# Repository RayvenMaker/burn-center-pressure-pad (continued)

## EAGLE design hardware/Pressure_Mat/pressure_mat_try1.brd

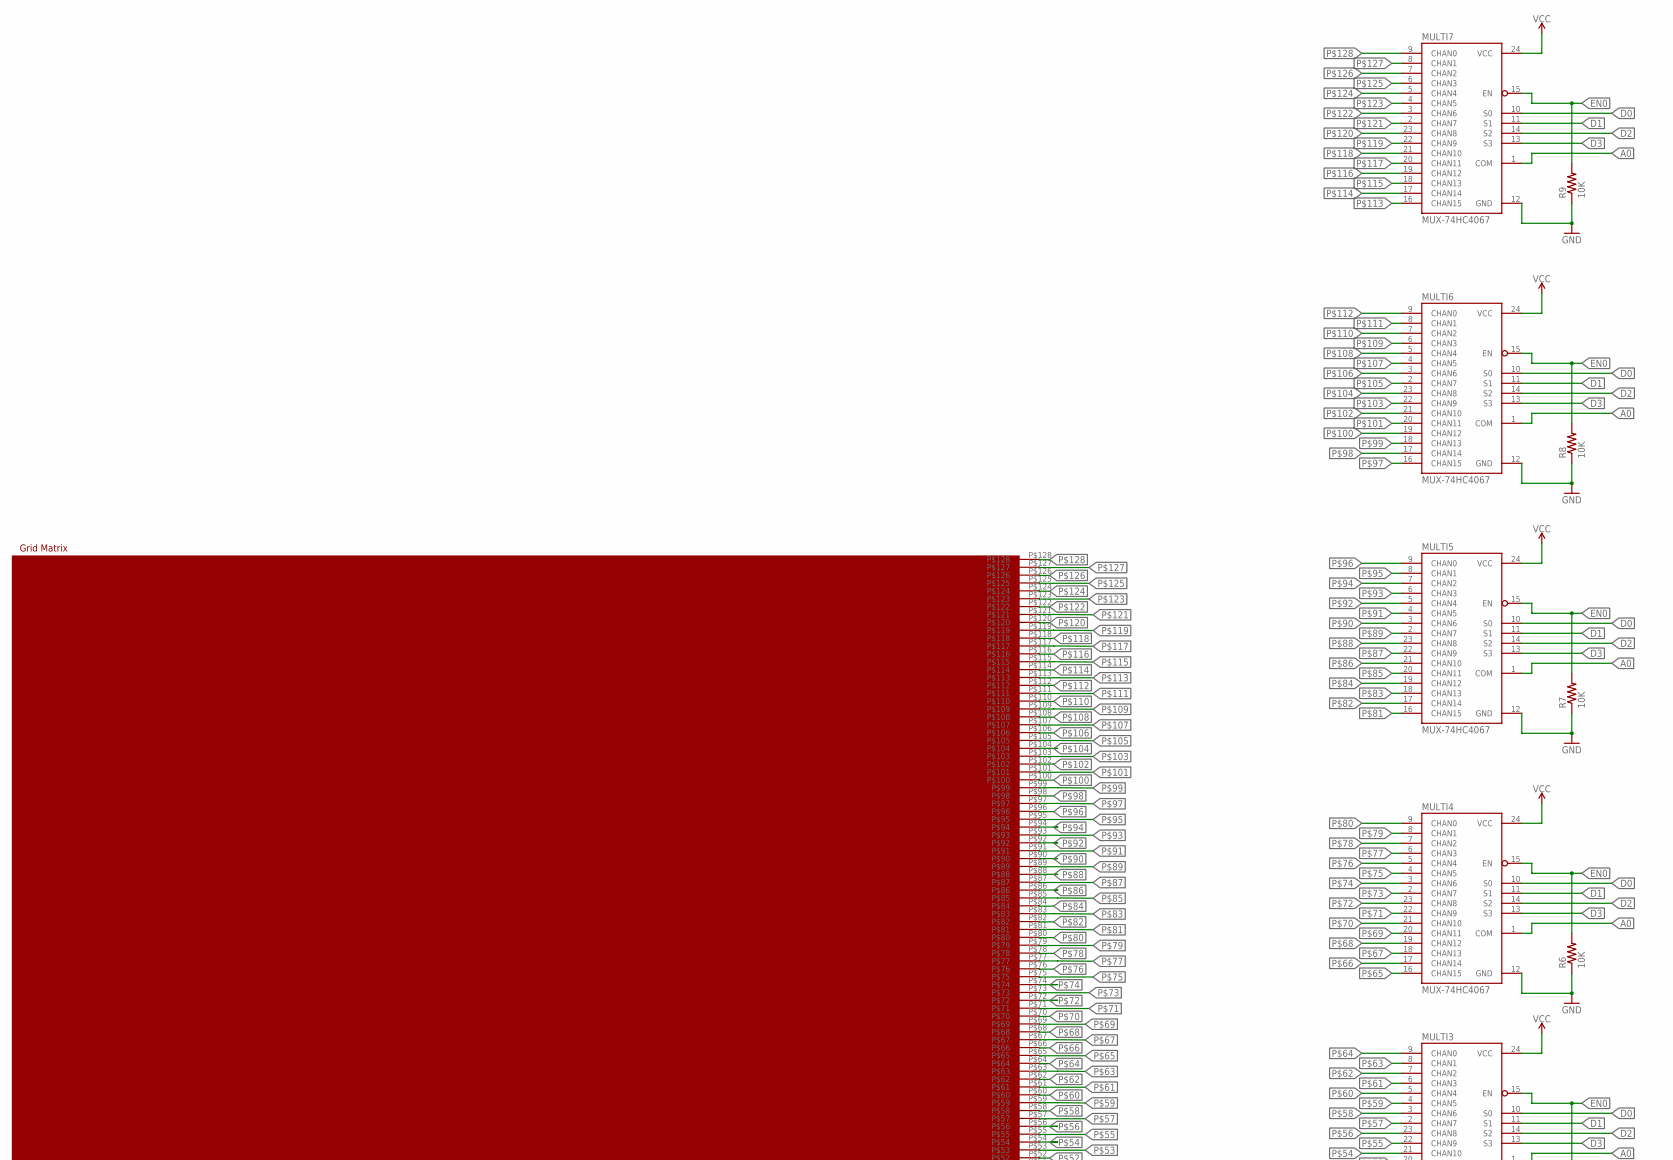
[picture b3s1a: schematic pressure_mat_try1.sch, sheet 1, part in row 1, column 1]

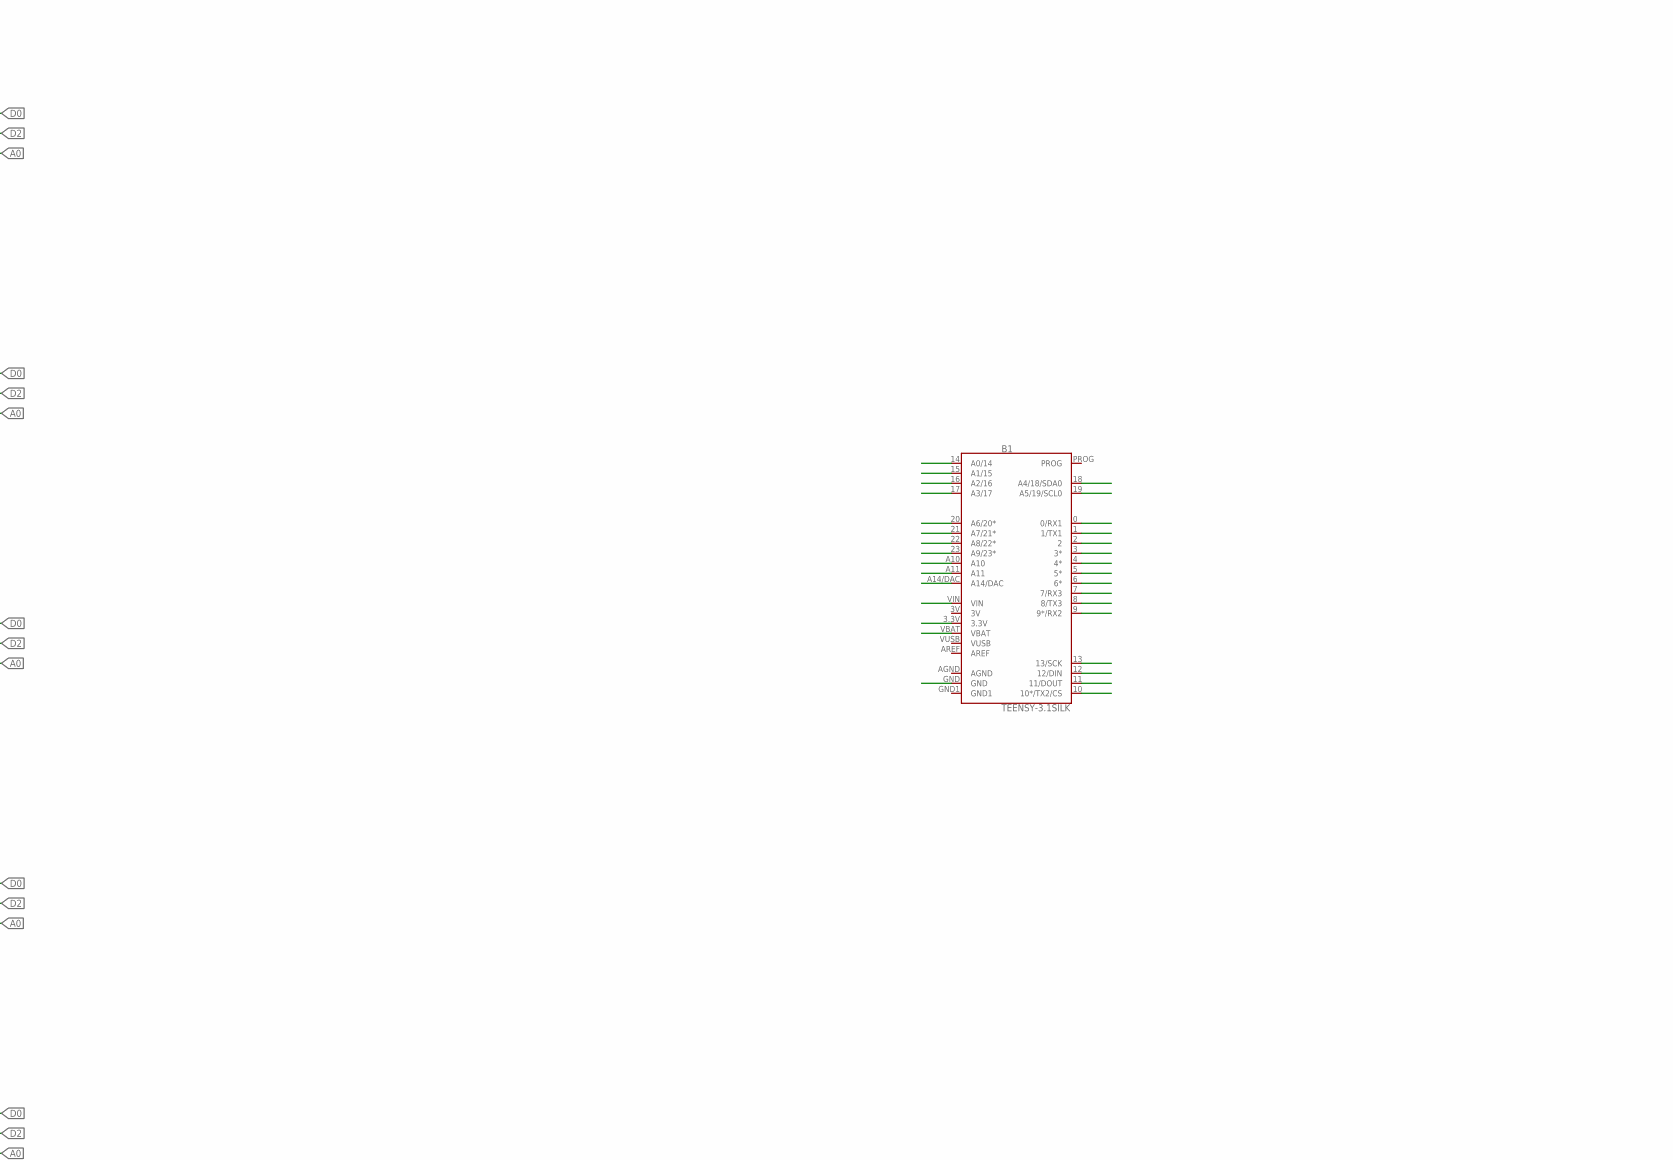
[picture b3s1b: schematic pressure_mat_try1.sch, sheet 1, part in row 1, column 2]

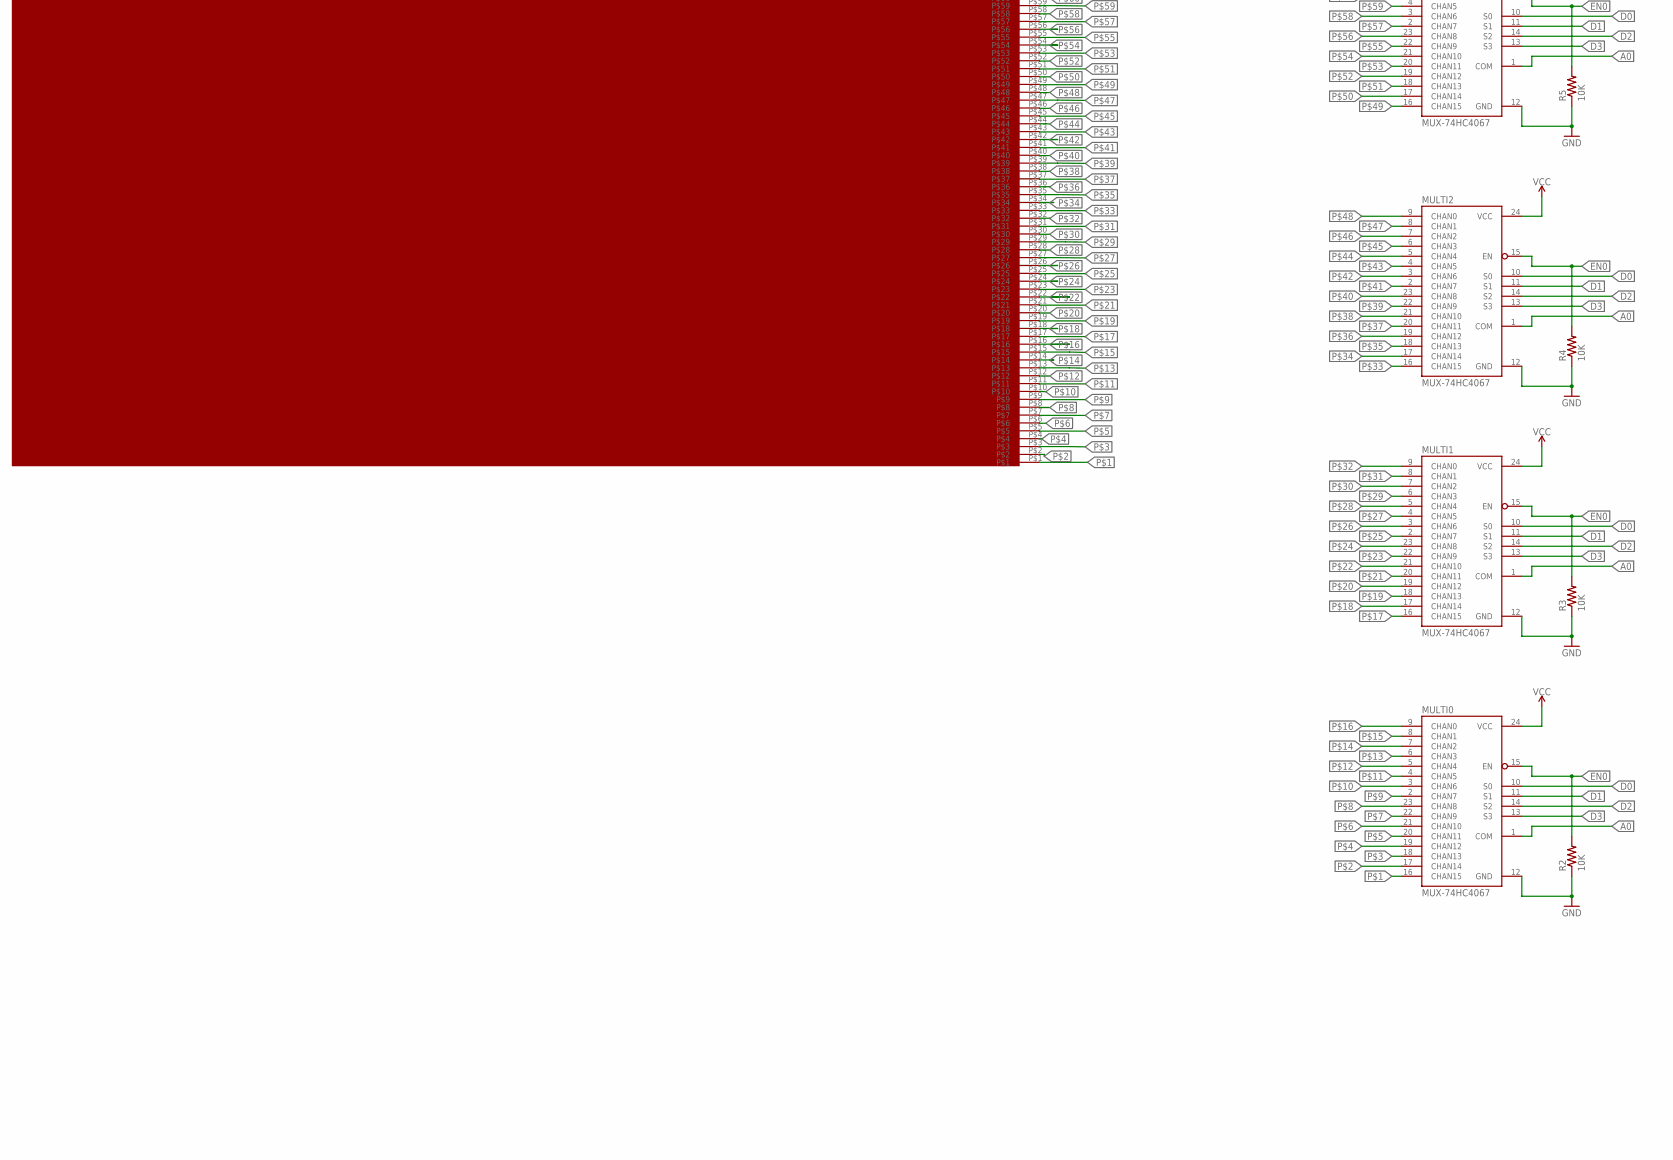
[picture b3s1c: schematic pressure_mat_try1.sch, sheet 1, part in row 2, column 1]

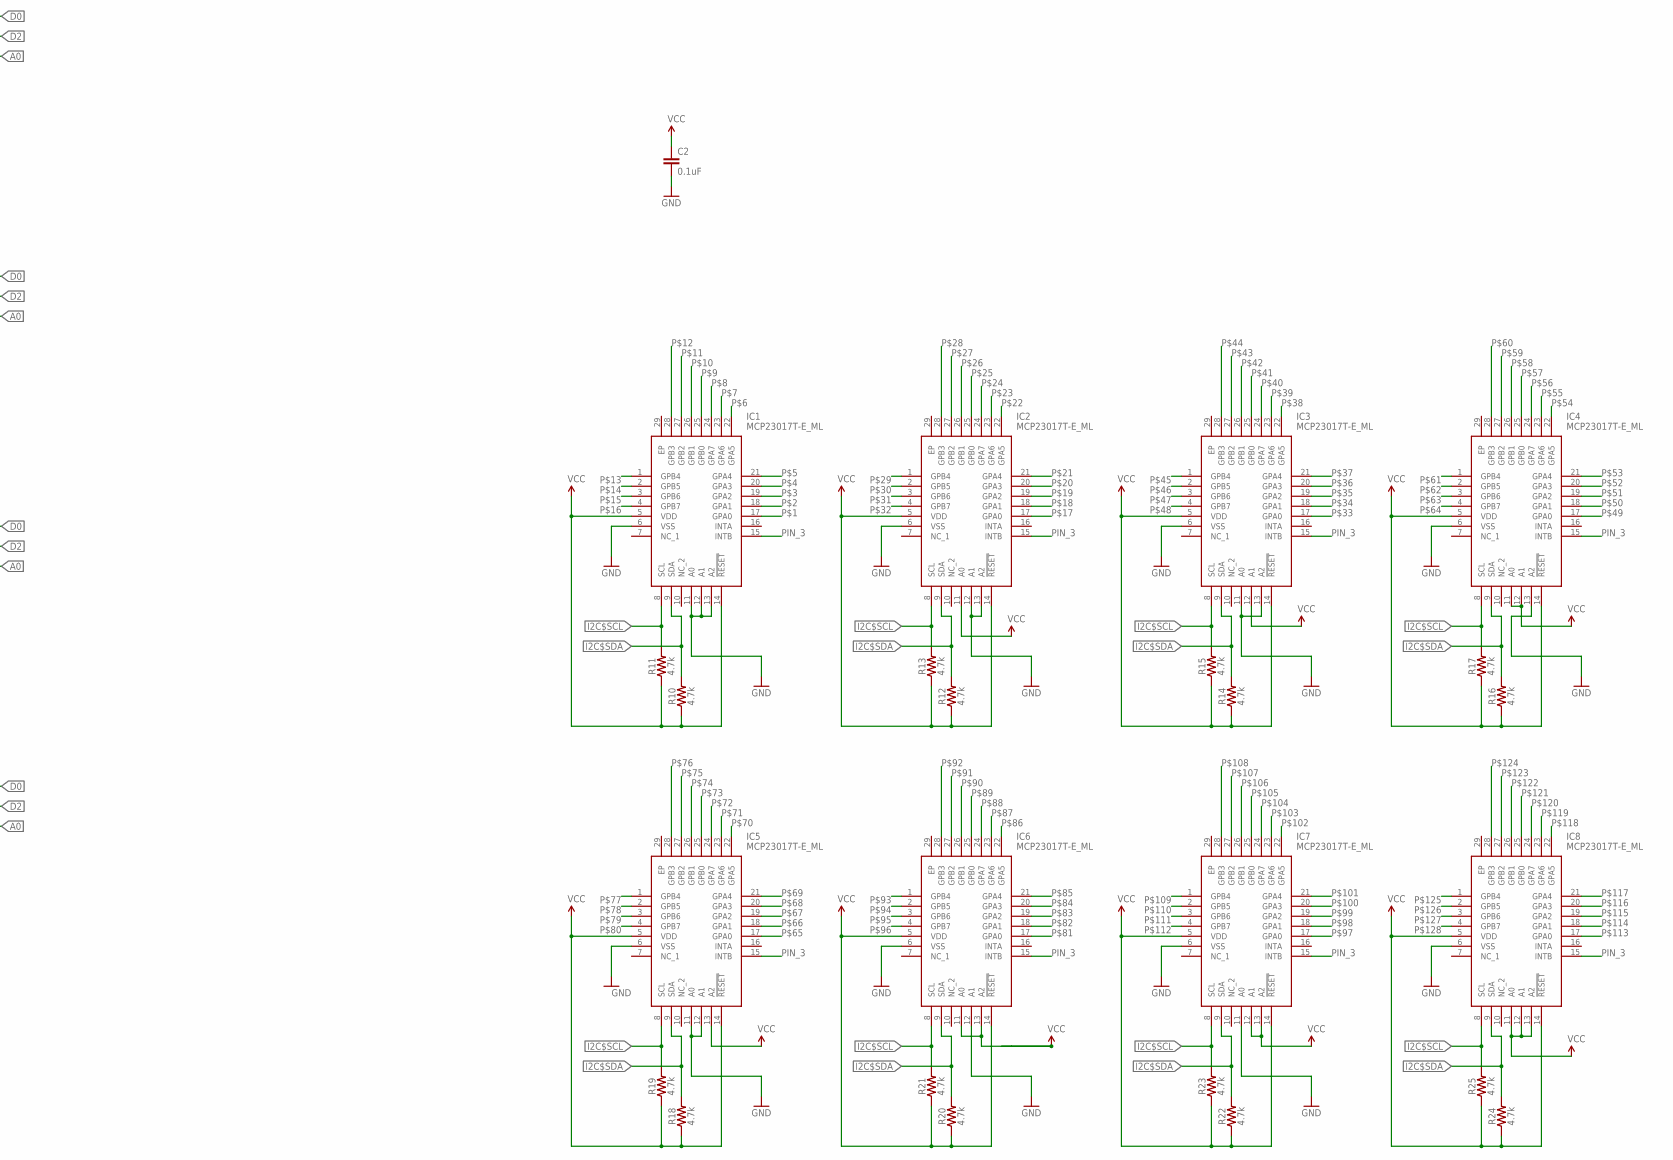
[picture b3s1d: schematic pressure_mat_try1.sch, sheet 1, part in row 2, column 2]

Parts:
B1: TEENSY-3.1SILK; TEENSY-3.1
C2: 0.1uF; 0603
IC1, IC2, IC3, IC4, IC5, IC6, IC7, IC8: MCP23017T-E_ML; QFN65P600X600X100-29N
MULTI0, MULTI1, MULTI2, MULTI3, MULTI4, MULTI5, MULTI6, MULTI7: MUX-74HC4067; SSOP24
R2, R3, R4, R5, R6, R7, R8, R9: 10K; 0603
R10, R11, R12, R13, R14, R15, R16, R17, R18, R19, R20, R21, R22, R23, R24, R25: 4.7k; 0603
U$3: SENSOR_GRID_V1.0

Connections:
3V: B1.3V
A0: MULTI0.1 (COM), MULTI1.1 (COM), MULTI2.1 (COM), MULTI3.1 (COM), MULTI4.1 (COM), MULTI5.1 (COM), MULTI6.1 (COM), MULTI7.1 (COM)
AGND: B1.AGND
D0: MULTI0.10 (S0), MULTI1.10 (S0), MULTI2.10 (S0), MULTI3.10 (S0), MULTI4.10 (S0), MULTI5.10 (S0), MULTI6.10 (S0), MULTI7.10 (S0)
D1: MULTI0.11 (S1), MULTI1.11 (S1), MULTI2.11 (S1), MULTI3.11 (S1), MULTI4.11 (S1), MULTI5.11 (S1), MULTI6.11 (S1), MULTI7.11 (S1)
D2: MULTI0.14 (S2), MULTI1.14 (S2), MULTI2.14 (S2), MULTI3.14 (S2), MULTI4.14 (S2), MULTI5.14 (S2), MULTI6.14 (S2), MULTI7.14 (S2)
D3: MULTI0.13 (S3), MULTI1.13 (S3), MULTI2.13 (S3), MULTI3.13 (S3), MULTI4.13 (S3), MULTI5.13 (S3), MULTI6.13 (S3), MULTI7.13 (S3)
EN0: MULTI0.15 (EN), MULTI1.15 (EN), MULTI2.15 (EN), MULTI3.15 (EN), MULTI4.15 (EN), MULTI5.15 (EN), MULTI6.15 (EN), MULTI7.15 (EN), R2.2, R3.2, R4.2, R5.2, R6.2, R7.2, R8.2, R9.2
GND: C2.2, IC1.6 (VSS), IC1.11 (A0), IC1.12 (A1), IC1.13 (A2), IC2.6 (VSS), IC2.12 (A1), IC2.13 (A2), IC3.6 (VSS), IC3.11 (A0), IC3.13 (A2), IC4.6 (VSS), IC4.13 (A2), IC5.6 (VSS), IC5.11 (A0), IC5.12 (A1), IC6.6 (VSS), IC6.12 (A1), IC7.6 (VSS), IC7.11 (A0), IC8.6 (VSS), MULTI0.12 (GND), MULTI1.12 (GND), MULTI2.12 (GND), MULTI3.12 (GND), MULTI4.12 (GND), MULTI5.12 (GND), MULTI6.12 (GND), MULTI7.12 (GND), R2.1, R3.1, R4.1, R5.1, R6.1, R7.1, R8.1, R9.1; also elsewhere on the board
GND1: B1.GND1
I2C$SCL: IC1.8 (SCL), IC2.8 (SCL), IC3.8 (SCL), IC4.8 (SCL), IC5.8 (SCL), IC6.8 (SCL), IC7.8 (SCL), IC8.8 (SCL), R11.2, R13.2, R15.2, R17.2, R19.2, R21.2, R23.2, R25.2
I2C$SDA: IC1.9 (SDA), IC2.9 (SDA), IC3.9 (SDA), IC4.9 (SDA), IC5.9 (SDA), IC6.9 (SDA), IC7.9 (SDA), IC8.9 (SDA), R10.2, R12.2, R14.2, R16.2, R18.2, R20.2, R22.2, R24.2
P$1: IC1.17 (GPA0), MULTI0.16 (CHAN15), U$3.P$1
P$2: IC1.18 (GPA1), MULTI0.17 (CHAN14), U$3.P$2
P$3: IC1.19 (GPA2), MULTI0.18 (CHAN13), U$3.P$3
P$4: IC1.20 (GPA3), MULTI0.19 (CHAN12), U$3.P$4
P$5: IC1.21 (GPA4), MULTI0.20 (CHAN11), U$3.P$5
P$6: IC1.22 (GPA5), MULTI0.21 (CHAN10), U$3.P$6
P$7: IC1.23 (GPA6), MULTI0.22 (CHAN9), U$3.P$7
P$8: IC1.24 (GPA7), MULTI0.23 (CHAN8), U$3.P$8
P$9: IC1.25 (GPB0), MULTI0.2 (CHAN7), U$3.P$9
P$10: IC1.26 (GPB1), MULTI0.3 (CHAN6), U$3.P$10
P$11: IC1.27 (GPB2), MULTI0.4 (CHAN5), U$3.P$11
P$12: IC1.28 (GPB3), MULTI0.5 (CHAN4), U$3.P$12
P$13: IC1.1 (GPB4), MULTI0.6 (CHAN3), U$3.P$13
P$14: IC1.2 (GPB5), MULTI0.7 (CHAN2), U$3.P$14
P$15: IC1.3 (GPB6), MULTI0.8 (CHAN1), U$3.P$15
P$16: IC1.4 (GPB7), MULTI0.9 (CHAN0), U$3.P$16
P$17: IC2.17 (GPA0), MULTI1.16 (CHAN15), U$3.P$17
P$18: IC2.18 (GPA1), MULTI1.17 (CHAN14), U$3.P$18
P$19: IC2.19 (GPA2), MULTI1.18 (CHAN13), U$3.P$19
P$20: IC2.20 (GPA3), MULTI1.19 (CHAN12), U$3.P$20
P$21: IC2.21 (GPA4), MULTI1.20 (CHAN11), U$3.P$21
P$22: IC2.22 (GPA5), MULTI1.21 (CHAN10), U$3.P$22
P$23: IC2.23 (GPA6), MULTI1.22 (CHAN9), U$3.P$23
P$24: IC2.24 (GPA7), MULTI1.23 (CHAN8), U$3.P$24
P$25: IC2.25 (GPB0), MULTI1.2 (CHAN7), U$3.P$25
P$26: IC2.26 (GPB1), MULTI1.3 (CHAN6), U$3.P$26
P$27: IC2.27 (GPB2), MULTI1.4 (CHAN5), U$3.P$27
P$28: IC2.28 (GPB3), MULTI1.5 (CHAN4), U$3.P$28
P$29: IC2.1 (GPB4), MULTI1.6 (CHAN3), U$3.P$29
P$30: IC2.2 (GPB5), MULTI1.7 (CHAN2), U$3.P$30
P$31: IC2.3 (GPB6), MULTI1.8 (CHAN1), U$3.P$31
P$32: IC2.4 (GPB7), MULTI1.9 (CHAN0), U$3.P$32
P$33: IC3.17 (GPA0), MULTI2.16 (CHAN15), U$3.P$33
P$34: IC3.18 (GPA1), MULTI2.17 (CHAN14), U$3.P$34
P$35: IC3.19 (GPA2), MULTI2.18 (CHAN13), U$3.P$35
P$36: IC3.20 (GPA3), MULTI2.19 (CHAN12), U$3.P$36
P$37: IC3.21 (GPA4), MULTI2.20 (CHAN11), U$3.P$37
P$38: IC3.22 (GPA5), MULTI2.21 (CHAN10), U$3.P$38
P$39: IC3.23 (GPA6), MULTI2.22 (CHAN9), U$3.P$39
P$40: IC3.24 (GPA7), MULTI2.23 (CHAN8), U$3.P$40
P$41: IC3.25 (GPB0), MULTI2.2 (CHAN7), U$3.P$41
P$42: IC3.26 (GPB1), MULTI2.3 (CHAN6), U$3.P$42
P$43: IC3.27 (GPB2), MULTI2.4 (CHAN5), U$3.P$43
P$44: IC3.28 (GPB3), MULTI2.5 (CHAN4), U$3.P$44
P$45: IC3.1 (GPB4), MULTI2.6 (CHAN3), U$3.P$45
P$46: IC3.2 (GPB5), MULTI2.7 (CHAN2), U$3.P$46
P$47: IC3.3 (GPB6), MULTI2.8 (CHAN1), U$3.P$47
P$48: IC3.4 (GPB7), MULTI2.9 (CHAN0), U$3.P$48
P$49: IC4.17 (GPA0), MULTI3.16 (CHAN15), U$3.P$49
P$50: IC4.18 (GPA1), MULTI3.17 (CHAN14), U$3.P$50
P$51: IC4.19 (GPA2), MULTI3.18 (CHAN13), U$3.P$51
P$52: IC4.20 (GPA3), MULTI3.19 (CHAN12), U$3.P$52
P$53: IC4.21 (GPA4), MULTI3.20 (CHAN11), U$3.P$53
P$54: IC4.22 (GPA5), MULTI3.21 (CHAN10), U$3.P$54
P$55: IC4.23 (GPA6), MULTI3.22 (CHAN9), U$3.P$55
P$56: IC4.24 (GPA7), MULTI3.23 (CHAN8), U$3.P$56
P$57: IC4.25 (GPB0), MULTI3.2 (CHAN7), U$3.P$57
P$58: IC4.26 (GPB1), MULTI3.3 (CHAN6), U$3.P$58
P$59: IC4.27 (GPB2), MULTI3.4 (CHAN5), U$3.P$59
P$60: IC4.28 (GPB3), MULTI3.5 (CHAN4), U$3.P$60
P$61: IC4.1 (GPB4), MULTI3.6 (CHAN3), U$3.P$61
P$62: IC4.2 (GPB5), MULTI3.7 (CHAN2), U$3.P$62
P$63: IC4.3 (GPB6), MULTI3.8 (CHAN1), U$3.P$63
P$64: IC4.4 (GPB7), MULTI3.9 (CHAN0), U$3.P$64
P$65: IC5.17 (GPA0), MULTI4.16 (CHAN15), U$3.P$65
P$66: IC5.18 (GPA1), MULTI4.17 (CHAN14), U$3.P$66
P$67: IC5.19 (GPA2), MULTI4.18 (CHAN13), U$3.P$67
P$68: IC5.20 (GPA3), MULTI4.19 (CHAN12), U$3.P$68
P$69: IC5.21 (GPA4), MULTI4.20 (CHAN11), U$3.P$69
P$70: IC5.22 (GPA5), MULTI4.21 (CHAN10), U$3.P$70
P$71: IC5.23 (GPA6), MULTI4.22 (CHAN9), U$3.P$71
P$72: IC5.24 (GPA7), MULTI4.23 (CHAN8), U$3.P$72
P$73: IC5.25 (GPB0), MULTI4.2 (CHAN7), U$3.P$73
P$74: IC5.26 (GPB1), MULTI4.3 (CHAN6), U$3.P$74
P$75: IC5.27 (GPB2), MULTI4.4 (CHAN5), U$3.P$75
P$76: IC5.28 (GPB3), MULTI4.5 (CHAN4), U$3.P$76
P$77: IC5.1 (GPB4), MULTI4.6 (CHAN3), U$3.P$77
P$78: IC5.2 (GPB5), MULTI4.7 (CHAN2), U$3.P$78
P$79: IC5.3 (GPB6), MULTI4.8 (CHAN1), U$3.P$79
P$80: IC5.4 (GPB7), MULTI4.9 (CHAN0), U$3.P$80
P$81: IC6.17 (GPA0), MULTI5.16 (CHAN15), U$3.P$81
P$82: IC6.18 (GPA1), MULTI5.17 (CHAN14), U$3.P$82
P$83: IC6.19 (GPA2), MULTI5.18 (CHAN13), U$3.P$83
P$84: IC6.20 (GPA3), MULTI5.19 (CHAN12), U$3.P$84
P$85: IC6.21 (GPA4), MULTI5.20 (CHAN11), U$3.P$85
P$86: IC6.22 (GPA5), MULTI5.21 (CHAN10), U$3.P$86
P$87: IC6.23 (GPA6), MULTI5.22 (CHAN9), U$3.P$87
P$88: IC6.24 (GPA7), MULTI5.23 (CHAN8), U$3.P$88
P$89: IC6.25 (GPB0), MULTI5.2 (CHAN7), U$3.P$89
P$90: IC6.26 (GPB1), MULTI5.3 (CHAN6), U$3.P$90
P$91: IC6.27 (GPB2), MULTI5.4 (CHAN5), U$3.P$91
P$92: IC6.28 (GPB3), MULTI5.5 (CHAN4), U$3.P$92
P$93: IC6.1 (GPB4), MULTI5.6 (CHAN3), U$3.P$93
P$94: IC6.2 (GPB5), MULTI5.7 (CHAN2), U$3.P$94
P$95: IC6.3 (GPB6), MULTI5.8 (CHAN1), U$3.P$95
P$96: IC6.4 (GPB7), MULTI5.9 (CHAN0), U$3.P$96
P$97: IC7.17 (GPA0), MULTI6.16 (CHAN15), U$3.P$97
P$98: IC7.18 (GPA1), MULTI6.17 (CHAN14), U$3.P$98
P$99: IC7.19 (GPA2), MULTI6.18 (CHAN13), U$3.P$99
P$100: IC7.20 (GPA3), MULTI6.19 (CHAN12), U$3.P$100
P$101: IC7.21 (GPA4), MULTI6.20 (CHAN11), U$3.P$101
P$102: IC7.22 (GPA5), MULTI6.21 (CHAN10), U$3.P$102
P$103: IC7.23 (GPA6), MULTI6.22 (CHAN9), U$3.P$103
P$104: IC7.24 (GPA7), MULTI6.23 (CHAN8), U$3.P$104
P$105: IC7.25 (GPB0), MULTI6.2 (CHAN7), U$3.P$105
P$106: IC7.26 (GPB1), MULTI6.3 (CHAN6), U$3.P$106
P$107: IC7.27 (GPB2), MULTI6.4 (CHAN5), U$3.P$107
P$108: IC7.28 (GPB3), MULTI6.5 (CHAN4), U$3.P$108
P$109: IC7.1 (GPB4), MULTI6.6 (CHAN3), U$3.P$109
P$110: IC7.2 (GPB5), MULTI6.7 (CHAN2), U$3.P$110
P$111: IC7.3 (GPB6), MULTI6.8 (CHAN1), U$3.P$111
P$112: IC7.4 (GPB7), MULTI6.9 (CHAN0), U$3.P$112
P$113: IC8.17 (GPA0), MULTI7.16 (CHAN15), U$3.P$113
P$114: IC8.18 (GPA1), MULTI7.17 (CHAN14), U$3.P$114
P$115: IC8.19 (GPA2), MULTI7.18 (CHAN13), U$3.P$115
P$116: IC8.20 (GPA3), MULTI7.19 (CHAN12), U$3.P$116
P$117: IC8.21 (GPA4), MULTI7.20 (CHAN11), U$3.P$117
P$118: IC8.22 (GPA5), MULTI7.21 (CHAN10), U$3.P$118
P$119: IC8.23 (GPA6), MULTI7.22 (CHAN9), U$3.P$119
P$120: IC8.24 (GPA7), MULTI7.23 (CHAN8), U$3.P$120
P$121: IC8.25 (GPB0), MULTI7.2 (CHAN7), U$3.P$121
P$122: IC8.26 (GPB1), MULTI7.3 (CHAN6), U$3.P$122
P$123: IC8.27 (GPB2), MULTI7.4 (CHAN5), U$3.P$123
P$124: IC8.28 (GPB3), MULTI7.5 (CHAN4), U$3.P$124
P$125: IC8.1 (GPB4), MULTI7.6 (CHAN3), U$3.P$125
P$126: IC8.2 (GPB5), MULTI7.7 (CHAN2), U$3.P$126
P$127: IC8.3 (GPB6), MULTI7.8 (CHAN1), U$3.P$127
P$128: IC8.4 (GPB7), MULTI7.9 (CHAN0), U$3.P$128
PIN_3: IC1.15 (INTB), IC2.15 (INTB), IC3.15 (INTB), IC4.15 (INTB), IC5.15 (INTB), IC6.15 (INTB), IC7.15 (INTB), IC8.15 (INTB)
VCC: C2.1, IC1.5 (VDD), IC1.14 (!RESET), IC2.5 (VDD), IC2.11 (A0), IC2.14 (!RESET), IC3.5 (VDD), IC3.12 (A1), IC3.14 (!RESET), IC4.5 (VDD), IC4.11 (A0), IC4.12 (A1), IC4.14 (!RESET), IC5.5 (VDD), IC5.13 (A2), IC5.14 (!RESET), IC6.5 (VDD), IC6.11 (A0), IC6.13 (A2), IC6.14 (!RESET), IC7.5 (VDD), IC7.12 (A1), IC7.13 (A2), IC7.14 (!RESET), IC8.5 (VDD), IC8.11 (A0), IC8.12 (A1), IC8.13 (A2), IC8.14 (!RESET), MULTI0.24 (VCC), MULTI1.24 (VCC), MULTI2.24 (VCC), MULTI3.24 (VCC), MULTI4.24 (VCC), MULTI5.24 (VCC), MULTI6.24 (VCC), MULTI7.24 (VCC), R10.1, R11.1, R12.1, R13.1, R14.1, R15.1, R16.1, R17.1, R18.1, R19.1, R20.1, R21.1, R22.1, R23.1, R24.1, R25.1; also elsewhere on the board
VUSB: B1.VUSB

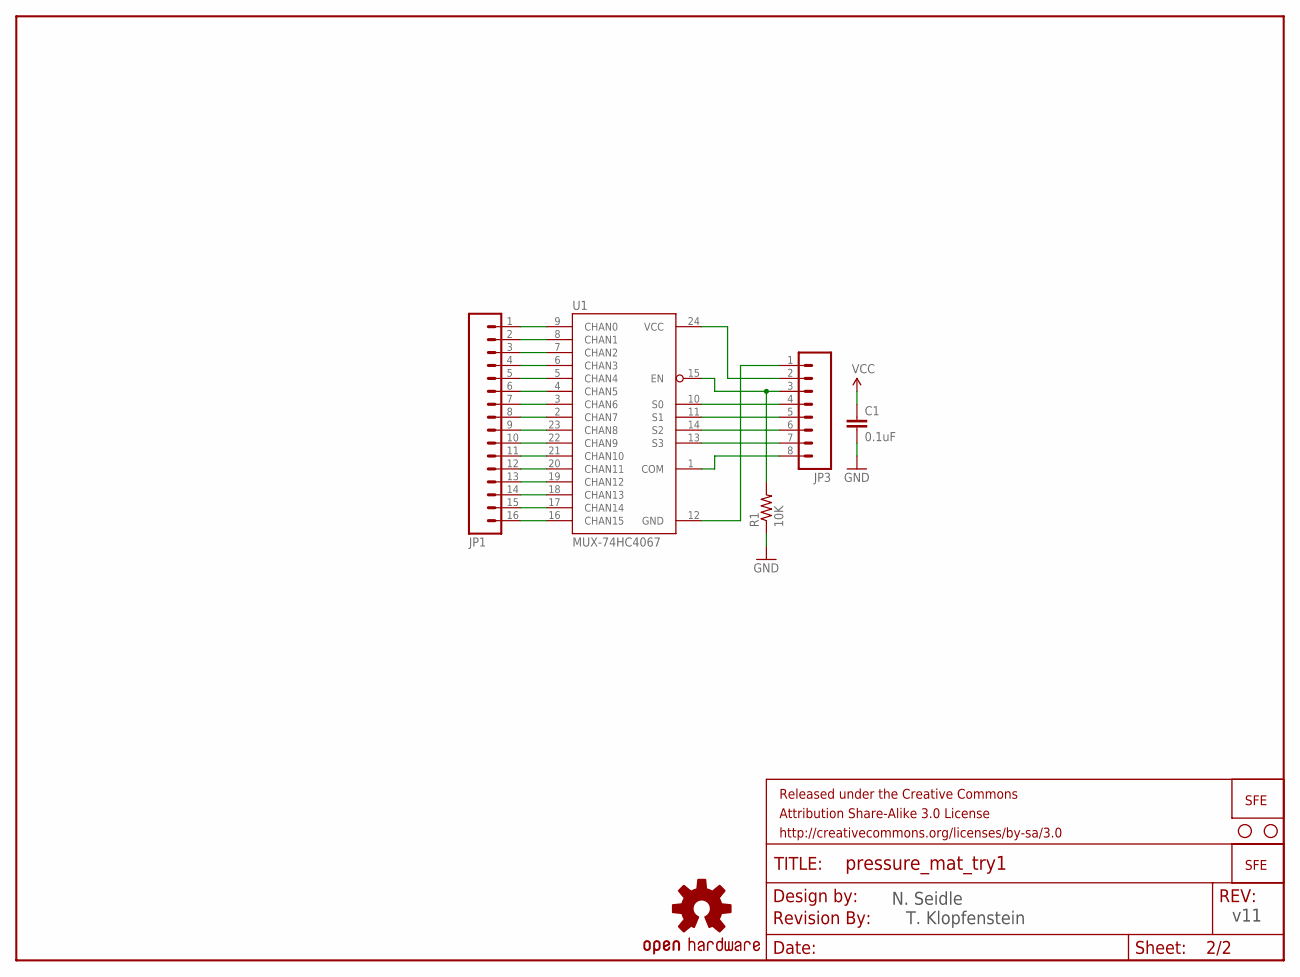
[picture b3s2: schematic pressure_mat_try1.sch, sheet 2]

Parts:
C1: 0.1uF; 0603
FRAME1: FRAME-LETTER; CREATIVE_COMMONS
JP1: M16PTH; 1X16
JP3: M081X08; 1X08
LOGO1: OSHW-LOGOL; OSHW-LOGO-L
LOGO2: LOGO-SFESK; SFE-LOGO-FLAME
R1: 10K; 0603
STANDOFF1, STANDOFF2: STAND-OFF
U1: MUX-74HC4067; SSOP24
U$1: LOGO-SFENEW; SFE-NEW-WEBLOGO
U$2: REVISION

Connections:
C0: JP1.1, U1.9 (CHAN0)
C1: JP1.2, U1.8 (CHAN1)
C2: JP1.3, U1.7 (CHAN2)
C3: JP1.4, U1.6 (CHAN3)
C4: JP1.5, U1.5 (CHAN4)
C5: JP1.6, U1.4 (CHAN5)
C6: JP1.7, U1.3 (CHAN6)
C7: JP1.8, U1.2 (CHAN7)
C8: JP1.9, U1.23 (CHAN8)
C9: JP1.10, U1.22 (CHAN9)
C10: JP1.11, U1.21 (CHAN10)
C11: JP1.12, U1.20 (CHAN11)
C12: JP1.13, U1.19 (CHAN12)
C13: JP1.14, U1.18 (CHAN13)
C14: JP1.15, U1.17 (CHAN14)
C15: JP1.16, U1.16 (CHAN15)
EN: JP3.3, R1.2, U1.15 (EN)
GND: C1.2, JP3.1, R1.1, U1.12 (GND); also elsewhere on the board
S0: JP3.4, U1.10 (S0)
S1: JP3.5, U1.11 (S1)
S2: JP3.6, U1.14 (S2)
S3: JP3.7, U1.13 (S3)
SIG: JP3.8, U1.1 (COM)
VCC: C1.1, JP3.2, U1.24 (VCC); also elsewhere on the board

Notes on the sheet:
v11
N. Seidle
T. Klopfenstein

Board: 2 copper layers, 55 parts (0 on the bottom side), 161 nets, no tracks yet.

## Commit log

2019-02-19 Initial upload.
2019-02-19 Uploaded new Eagle schematic and board
2019-02-20 Added README for the software folder.
2019-03-09 Added test program for 16x16 pad
2019-03-09 Update 16x16 test program
    - Added code to print pressure data to serial
2019-03-15 Added analog multiplexer test program
2019-05-01 Added revised schematic.
    Also ripped up the traces on the board, because there are some new components and we MIGHT be switching to ganged resistor networks
2019-05-02 Updated test programs
2019-05-03 new stuff
    new stuff
2019-05-08 Restructured software folder and added WIP Raspberry code
2019-05-08 Work on Raspberry Pi code
2019-05-09 Added copyright notices
2019-05-11 Work on code for 64x64 grid
    - Updated 64x64 grid code to properly cycle through MCP23017 I2C port expanders
    - Added modified version of code for Arduino Due
2019-05-23 Updates to 64x64 grid code
    - Rearranged Arduino folder
    - Added PressurePad64x64 and PressurePad64x64Testing. See software/README.md for more details.
    - Removed obsolete Raspberry Pi code
2019-06-22 Changed baud rates and set CS pin
2019-07-12 Added Rigid board files
2019-07-12 Wired up connectors
2019-07-24 Moved components to board
2019-07-25 Board redesign
    Removed a ton of resistors, added SMD headers, and simplfied board.
2019-07-25 Spaced out components
    what
2019-07-25 I'M TYPING WITH MY HANDS
2019-07-25 Removed flex pin connectors
